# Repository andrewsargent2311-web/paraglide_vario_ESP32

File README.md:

# Paraglide Vario / Flight Computer (ESP32-S3)

A DIY flight computer for paragliding and paramotoring that costs about **$60 USD** in parts. It has a sunlight-readable screen, a climb/sink beeper (vario), GPS, a barometer, airspace warnings, live ADS-B traffic with spoken voice alerts, weather stations, FANET radio and IGC flight logging. Note the RLCD screen does not work well with polarized glasses (found that out on my first paragliding flight, use ski goggles on the paramotor).

**You do not need any electronics or programming experience.** This guide walks through every step. If you can follow a recipe and are willing to learn to solder a few small parts (or find a friend who can), you can build this.

> ⚠️ **Safety:** This is a hobby project, not a certified flight instrument. Never rely on it as your only source of airspace, altitude or traffic information. Test everything on the ground before you fly with it.

---

## Contents

1. [What it does](#1-what-it-does)
2. [What you need to buy](#2-what-you-need-to-buy)
3. [Tools you need](#3-tools-you-need)
4. [Step 1: Order the circuit board](#step-1-order-the-circuit-board)
5. [Step 2: 3D print the case](#step-2-3d-print-the-case)
6. [Step 3: Solder the circuit board](#step-3-solder-the-circuit-board)
7. [Step 4: Install VS Code and PlatformIO](#step-4-install-vs-code-and-platformio)
8. [Step 5: Add your WiFi details](#step-5-add-your-wifi-details)
9. [Step 6: Build and upload the code](#step-6-build-and-upload-the-code)
10. [Step 7: Prepare the SD card](#step-7-prepare-the-sd-card)
11. [Step 8: Assemble everything](#step-8-assemble-everything)
12. [Step 9: First power-on check](#step-9-first-power-on-check)
13. [How to use it](#how-to-use-it)
14. [Voice traffic alerts](#voice-traffic-alerts)
15. [Cloud base estimate](#cloud-base-estimate)
16. [Optional extras](#optional-extras)
17. [Troubleshooting](#troubleshooting)
18. [Using it outside New Zealand](#using-it-outside-new-zealand)
19. [Code layout](#code-layout)
20. [Credits](#credits)

---

## 1. What it does

- **Vario:** beeps faster and higher as you climb, lower tones when you sink
- **Main flight screen:** altitude, height above ground (AGL), ground speed, heading, QNH, battery
- **Airspace:** warns you about nearby controlled airspace from an OpenAIP file
- **Cloud base estimate:** a rough guess of how high the cloud base is, worked out from the temperature, humidity and pressure sensors (see [Cloud base estimate](#cloud-base-estimate))
- **ADS-B page:** shows nearby aircraft on a radar-style display, with an icon for each aircraft type, smooth movement between updates and automatic zoom (see [The traffic page](#the-traffic-page))
- **Voice traffic alerts:** when an aircraft comes close, the speaker tells you where it is, e.g. *"Aircraft on your two o'clock, flying north west, at two thousand four hundred feet, one thousand two hundred feet above you, and is eight hundred meters away."* You can switch this to a siren, or turn it off (see [Voice traffic alerts](#voice-traffic-alerts))
- **Weather page:** wind from nearby weather stations (Zephyr) or from FANET
- **FANET:** sends and receives FANET radio messages, with preset messages you can broadcast
- **IGC flight logging** to the SD card, downloadable over WiFi
- **Optional:** connects by Bluetooth to a separate engine meter (RPM, cylinder temperature) for paramotor use

**One button** controls everything (see [How to use it](#how-to-use-it)).

## 2. What you need to buy

| Part | Approx. cost | Notes |
|---|---|---|
| [Waveshare ESP32-S3-RLCD-4.2](https://www.waveshare.com/esp32-s3-rlcd-4.2.htm) | $35 USD (includes shipping, buy on Aliexpress) | The "brain", screen, speaker driver, SD slot and battery holder all in one |
| [Adafruit BMP580](https://www.adafruit.com/product/6411) | $10 USD | Barometer, measures altitude change for the vario |
| [Waveshare LC76G GNSS module](https://www.waveshare.com/lc76g-gnss-module.htm) | $15 | GPS |
| Custom circuit board (PCB) from PCBWay | $10 | See [Step 1](#step-1-order-the-circuit-board) |
| 3D printer filament (PLA) | $5 | Orange in the photos, any colour works |
| microSD card, 8–16 GB | a few $ | Doesn't need to be bigger |
| **HT-RA62 LoRa radio module** | $7 USD (includes shipping) | [HT-RA62] (https://heltec.org/project/ht-ra62/) Soldered directly onto the PCB, used for FANET. *Not included in the original $60 estimate.* |
| **18650 lithium battery** | comes with waveshare board for extra $3| Fits in the holder on the Waveshare board. Use a good-quality protected cell. |
| **USB-C data cable** | | Must carry data, not just charge |

**Small parts for the PCB** (all size 0805 surface-mount):

| Qty | Part |
|---|---|
| 2 | 100 nF capacitor |
| 2 | 10 µF capacitor |
| 1 | 10 kΩ resistor |

You will also need some pin headers and/or sockets to connect the Waveshare board, BMP580 and GPS module to the PCB. The exact layout is shown in the [KiCad project](PCB%20files/ESP32%20vario_PCB_layout/).

**Total: roughly $80 USD**

> **Tip:** Buy everything from the same order window if you can. PCBs from PCBWay usually arrive in a couple of weeks, so order that first.

## 3. Tools you need

- **Soldering iron** with a fine tip, solder and flux (for the tiny 0805 parts and the LoRa module). A hot-air station makes this easier but is not required.
- **Tweezers** (for the small parts)
- **A 3D printer**, or use a print service / friend with one
- **A computer** (Windows, Mac or Linux) with a USB port and an internet connection (the first build downloads a few hundred MB of tools)
- **A microSD card reader**
- Small screwdrivers, and wire cutters

**Never soldered before?** The only genuinely fiddly parts are the 0805 capacitors/resistor and the HT-RA62 module. Watch a couple of "how to solder SMD 0805" videos and practise on a spare board first, or ask a local maker space or electronics-savvy friend to do just those parts.

**Time:** allow a weekend. The 3D printing (about 9.5 hours total) runs by itself.

---

## Step 1: Order the circuit board

The circuit board (PCB) connects all the modules together so you don't have to wire anything by hand.

1. Go to [pcbway.com](https://www.pcbway.com) and choose **Instant Quote**.
2. Upload the file [`PCB files/Gerber Files V2/ESP32 vario-B_PCB_.zip`](PCB%20files/Gerber%20Files%20V2/). It contains all the Gerber and drill files in one zip.
3. Leave the options at their defaults unless you have a preference (it is a simple two-layer board), and place the order.

The original design files (KiCad) are in [`PCB files/ESP32 vario_PCB_layout/`](PCB%20files/ESP32%20vario_PCB_layout/) if you want to modify the board.

## Step 2: 3D print the case

All files are in [`3D print Files/`](3D%20print%20Files/).

| Part | STL file | Print time (0.15 mm PLA, Prusa MK3S) |
|---|---|---|
| Main case | `Flight computer main case.stl` | 5 h 49 m |
| Back plate | `Flight computer back plate.stl` | 2 h 11 m |
| Base plate | `Flight computer base plate.stl` | 1 h 14 m |
| Button | `button.stl` | 8 m |
| Button (short) | `button_Short.stl` | 6 m |
| Button (long) | `button_Long.stl` | 9 m |

- If you have a **Prusa MK3S**, you can print the ready-made G-code in the `Prusa slicer G code` folder.
- For **any other printer**, open the `.stl` files in your printer's slicing software (Cura, PrusaSlicer, Bambu Studio, etc.) and use normal PLA settings at 0.15 mm layer height.
- Print all three buttons; you'll pick whichever length feels best when you assemble it.

## Step 3: Solder the circuit board

Work from the smallest parts to the biggest, and take your time. Solder joints should be shiny and cone-shaped, not blobs.

1. **Small surface-mount parts first:** the two 100 nF capacitors, two 10 µF capacitors and the 10 kΩ resistor. The reference labels (C1, C2, C3, C-GPS1, R1) are printed on the board. Use the [parts list](PCB%20files/ESP32%20vario_PCB_layout/ESP32%20vario.csv) to match them.
2. **HT-RA62 LoRa module (U1):** solder this onto its pads on the board. Check the orientation using the silkscreen and the photo above. Double-check no pins are bridged with solder.
3. **Headers:** solder the pin headers/sockets for the Waveshare board (U2), BMP580 (U3) and GPS (U4).
4. **Plug in the modules.** Make sure each one goes the right way round. Use the photos in [`Photos/`](Photos/) as a reference.

**Before going on, check:** with a magnifier, look at every solder joint for bridges (solder connecting two neighbouring pins) and for pins that missed the solder.

## Step 4: Install VS Code and PlatformIO

This project is built with **[PlatformIO](https://platformio.org/)** inside **Visual Studio Code** (VS Code). PlatformIO downloads the ESP32 tools and every library the project needs automatically, so there is nothing to install by hand except VS Code and one extension. All of the board settings (PSRAM, USB serial, etc.) are already saved in the project's `platformio.ini` file, so you don't need to set anything.

### 4.1 Install VS Code
Download **Visual Studio Code** from [code.visualstudio.com](https://code.visualstudio.com/) and install it.

### 4.2 Install the PlatformIO extension
1. Open VS Code and click the **Extensions** icon in the left sidebar (it looks like four squares), or press `Ctrl+Shift+X` (`Cmd+Shift+X` on Mac).
2. Search for **PlatformIO IDE** and click **Install**.
3. Wait for it to finish (it can take a few minutes the first time, and a progress message appears at the bottom right), then **restart VS Code** when it asks.
4. After the restart you should see a new **alien-head PlatformIO icon** in the left sidebar and a blue bar of icons along the bottom of the window.

### 4.3 Download this project
Either:

- On this GitHub page, click the green **Code** button → **Download ZIP**, then unzip it somewhere you can find it (for example your Documents folder), **or**
- If you use Git: `git clone` this repository.

### 4.4 Open the project
1. In VS Code choose **File → Open Folder…**
2. Select the **top-level project folder**, the one that contains `platformio.ini` (not the `paraglide_vario_ESP32` folder inside it).
3. If VS Code asks *"Do you trust the authors of the files in this folder?"*, click **Yes, I trust the authors**.
4. PlatformIO now sets itself up. In the bottom-right you'll see messages such as *"Configuring project"* and *"Installing platform / libraries"*. **Wait until they finish.** The first time this downloads the ESP32 platform and all the libraries listed below, so it can take 5–15 minutes depending on your internet.

**Libraries installed for you automatically** (listed in `platformio.ini`; you never have to do this yourself):

| Library | Author |
|---|---|
| Adafruit BMP5xx | Adafruit |
| Adafruit SHTC3 | Adafruit |
| Adafruit Unified Sensor | Adafruit |
| ArduinoJson | Benoit Blanchon |
| NimBLE-Arduino | h2zero |
| RadioLib | Jan Gromeš |
| TinyGPSPlus | Mikal Hart |
| U8g2 (screen) | olikraus |
| Soldered PCF85063A RTC Library (clock) | Soldered |

> **Linux users:** to upload you need permission to use the USB serial port. Add yourself to the `dialout` group (`sudo usermod -aG dialout $USER`), then log out and back in. If it still can't see the board, install the PlatformIO udev rules (see the [PlatformIO docs](https://docs.platformio.org/en/latest/core/installation/udev-rules.html)).

## Step 5: Add your WiFi details

The code expects a file called `secrets.h` containing your WiFi network names and passwords. It is deliberately not uploaded to GitHub (so passwords don't leak), so you have to create it.

1. In VS Code's **Explorer** (the file list on the left, top icon in the sidebar), open the **`paraglide_vario_ESP32`** folder.
2. Right-click **`secrets.example.h`** → **Copy**, then right-click in an empty part of the same folder → **Paste**.
3. Right-click the copy (it will be named something like `secrets.example copy.h`) → **Rename**, and call it exactly **`secrets.h`**.
4. Open `secrets.h` and put in your details, for example:

```cpp
static const WifiNetwork WIFI_NETWORKS[WIFI_NETWORK_COUNT] = {
  { "MyHomeWiFi",     "my-home-password" },
  { "MyPhoneHotspot", "hotspot-password" },
  { "",               "" },
};
```

5. Save the file (`Ctrl+S`).

- Use a **2.4 GHz** network. The ESP32 can't connect to 5 GHz WiFi.
- Leave unused slots as empty quotes `""`.
- A **phone hotspot** is handy at the launch site, since that's how the ADS-B traffic and weather pages get their data in the field.
- You can also add networks later **from your phone, without reflashing**. See [Adding a WiFi network from your phone](#adding-a-wifi-network-from-your-phone).

## Step 6: Build and upload the code

1. Plug the Waveshare board into your computer with the USB-C data cable.
2. Look at the blue bar along the bottom of VS Code. The important icons are:

| Icon (hover to see its name) | What it does |
|---|---|
| ✓ **PlatformIO: Build** | Compiles the code without uploading it |
| → **PlatformIO: Upload** | Compiles and uploads to the board |
| 🔌 **PlatformIO: Serial Monitor** | Shows the messages the board prints (see Step 9) |

   You can also click the **PlatformIO (alien head) icon** in the left sidebar → **Project Tasks → esp32-s3 → General → Upload**.

3. Click **Upload** (the right-pointing arrow). The first build takes several minutes because it compiles every library.
4. When the terminal at the bottom says **`[SUCCESS]`**, the code is on your device. The board restarts by itself.

**What's already configured for you in `platformio.ini`** (you don't need to change any of this, but it's here in case you wonder):

| Setting | Value | Why |
|---|---|---|
| Board | `esp32-s3-devkitc-1` (ESP32-S3) | Matches the Waveshare board's chip |
| Platform | pioarduino (Arduino core 3.x for ESP32) | Required by the project's libraries |
| PSRAM | OPI PSRAM (`qio_opi` + `BOARD_HAS_PSRAM`) | The voice-alert clips are loaded into PSRAM |
| USB serial | `ARDUINO_USB_CDC_ON_BOOT=1` | Lets the Serial Monitor work over the USB-C port |
| Monitor speed | 115200 | Matches the code |

**If the upload doesn't start:** hold the **BOOT** button on the board, tap **RESET**, then release BOOT, and click Upload again. PlatformIO finds the port automatically. If you have several USB serial devices plugged in and it picks the wrong one, you can add a line such as `upload_port = COM5` (Windows) or `upload_port = /dev/ttyACM0` (Linux/Mac) under `[env:esp32-s3]` in `platformio.ini`.

> **Ignore the `native` environment.** `platformio.ini` also contains an `[env:native]` section. That is only for running the code's unit tests on a PC (`pio test -e native`) and isn't used when building for the device. If PlatformIO asks which environment to use, choose **esp32-s3**.

## Step 7: Prepare the SD card

1. **Format** the microSD card as **FAT32**.
2. Copy the files you want from [`paraglide_vario_ESP32/Goes into SD card/`](paraglide_vario_ESP32/Goes%20into%20SD%20card/) onto the **root** of the card. The two files go straight onto the card, but the **`VOICE` folder must be copied as a folder**, with the clips inside it:

| File / folder | What it's for |
|---|---|
| `AIRSPACE.txt` | Airspace data, used for warnings |
| `Lower_North_Island.ADEM` | Terrain height map, used to work out your height above ground (AGL). It's about 99 MB. |
| `VOICE/` (folder) | The 60 short speech clips (`V000.PCM` to `V059.PCM`) used for [voice traffic alerts](#voice-traffic-alerts). Flat `/VOICE/V###.PCM` files are the **Default** voice; optional profiles go in subfolders such as `/VOICE/US_RYAN/V000.PCM`. |

3. Eject the card safely and put it into the microSD slot on the Waveshare board.

**Notes:**
- The vario still works without the SD card, but you won't get flight logs, maps, airspace or voice alerts.
- All 60 clips must be present in a profile folder or that profile is skipped. The existing flat `/VOICE/V###.PCM` layout is still supported as **Default**. Put additional voices in `/VOICE/<NAME>/` folders; profile names may use letters, numbers, `_` and `-`, up to 12 characters. The device can list up to 8 profiles. `manifest.txt` is just a list of what each clip says and is ignored by the device.
- Generate additional profiles with the [`voicebuild` tool](voicebuild/README.md). Copy each generated profile folder into `VOICE/` on the card.
- You can keep several `.ADEM` maps on the card and choose between them from the menu (**Map**).
- The included airspace and terrain files cover the lower North Island of New Zealand. See [Optional extras](#optional-extras) for other areas.
- An optional splash image can be shown at startup: a file called `ROY.BIN` in the card root, a full-screen 300 × 400 black-and-white image of exactly 15,200 bytes. If it's missing or a different size, a plain text splash screen is shown instead, so you can skip this.

## Step 8: Assemble everything

1. Fit the **18650 battery** into the holder on the Waveshare board (check the +/− direction printed on the holder).
2. Plug the **speaker** into its 2-pin socket.
3. Push the Waveshare board onto the PCB, making sure the pins are lined up.
4. Connect the GPS and BMP580 modules to the PCB, and attach the antenna to the LoRa module.
5. Fit the board sandwich into the 3D-printed **main case**, then close it with the **back plate** and **base plate**.
6. Push the printed **button** into place over the button on the board. Try the three button lengths and use whichever feels best.

The GPS "bump" on the case (marked "GPS") should face the sky when you hold the unit flat, so the GPS gets a clear view.

Look at the photos in the [`Photos/`](Photos/) folder if you're unsure how something fits.

## Step 9: First power-on check

Do this indoors first, then repeat outside.

1. Switch on / plug in the unit. The **splash screen** appears for about 3 seconds, then the main screen.
2. Move the unit up and down by about a metre. You should hear the **vario beep** and see the altitude change.
3. Take it **outside with a clear view of the sky**. The first GPS lock can take a few minutes. Once it locks, speed, heading and time appear.
4. Look at the **AIR SPACE** box on the main screen. After the first temperature/humidity reading (about 10 seconds) and once the GPS has calibrated the altitude, the **CLD BASE** line shows a number. Until then it shows `--`. See [Cloud base estimate](#cloud-base-estimate) to calibrate it.
5. To see what the device is doing while it boots, click the **Serial Monitor** (🔌 plug icon) in the blue bar at the bottom of VS Code while the unit is plugged into your computer. It runs at **115200** baud automatically. It prints messages showing whether the SD card, barometer, GPS and radio all started correctly. If voice clips loaded you will see `[Voice] Loaded 60 voice clips into PSRAM (profile: Default)` or the name of the selected profile. Click the bin/trash or press `Ctrl+C` in the terminal to close the monitor, and **close it before you upload again** (the upload can't use the port while the monitor has it open).

---

## How to use it

The unit has **one button**:

| Menu | Press | What happens |
|---|---|---|
| Closed | **Short press** | Switch to the next page (Glider → Wind → ADS-B) |
| Closed | **Double press** | Open the menu |
| Closed | **Hold ~4 seconds** | Mute / unmute the vario |
| Open | **Short press** | Move down to the next menu item |
| Open | **Hold ~2 seconds** | Select the highlighted item |
| Open | **Double press** | Go back one level (or close the menu from the top level) |

**Menu contents**

- **Main Page:** choose Paraglider or Paramotor as the first page
- **Config:** time zone, units (altitude / speed), main volume, vario beep (climb and sink volume), lift threshold (climb beeps start above this: 0.0–1.0 m/s in 0.1 steps, default 0.1), screen orientation
- **Connections:** WiFi on/off, network choice, **Add Network** and **Forget Network** (see below), Bluetooth (engine meter), FANET on/off
- **FANET Messaging:** messaging on/off, and the preset messages you can broadcast
- **Map:** choose which terrain map to use
- **ADS-B settings:** alert radius and vertical threshold, auto-jump to the ADS-B page, **Alarm Sound** (Off / Alarm / Voice), **Alert Volume**, range rings, airspace bars, **Voice** profile, **Ground Traffic** and **Labels** (see [The traffic page](#the-traffic-page))
- **Weather settings:** update interval, number of stations, data source
- **Flight recordings:** recording on/off, **Export files** (see below), auto-stop, **Flights** (see below)

**Flight logs:** the unit automatically starts recording an `.IGC` file when you start moving (above about 10 km/h for 10 seconds). To download logs, open **Flight recordings → Export files**. Once the unit is connected to WiFi it shows a web address (something like `http://192.168.x.x/`). Open that in a browser on a phone or computer on the same network and click the file to download. If the server can't start, the screen tells you why: **WiFi not connected**, or **No SD card** (insert one and restart the unit, as it only checks for a card when it starts up).

The same page also lets you:
- **Delete** old flight recordings (asks to confirm first).
- **Upload** a new `.ADEM` terrain map or a replacement `AIRSPACE.txt` straight to the SD card, so you don't need to take the card out. Large maps take several minutes over WiFi, so do it on the ground. Then pick the new map from **Menu → Map**. After replacing `AIRSPACE.txt`, restart the unit, as airspace only loads at start-up.
- **Delete** maps you no longer need (the map currently in use can't be deleted or replaced; choose a different one in the Map menu first).

A script can load the rest of a card over the same connection. `POST /upload?path=ROY.BIN` or `POST /upload?path=VOICE/US_LESSAC/V000.PCM` (a multipart form with a `file` field) adds the splash image and voice files, creating the voice folders if needed. `GET /list` returns every file's path and size for checking. Restart the unit afterwards so it loads them.

Deleting and uploading are switched off while a flight is being recorded. Tracks are recorded at **one point per second**.

**Flights:** **Flight recordings → Flights** lists your 12 most recent flights, newest first, with the date, take-off time, duration, maximum altitude and best climb. Take-off time is when recording started, so it may be earlier than your actual take-off if the unit was already moving, for example in a car on the way to launch. Summaries are saved to `FLIGHTS.CSV` on the SD card about once a minute during a flight, so turning the unit off loses at most the last minute of the summary, and the IGC file itself isn't affected. Flights recorded before this feature show only the date, time and duration.

---

## Adding a WiFi network from your phone

You can add a network (for example a friend's hotspot, or the WiFi at a new launch site) straight from the unit, with no computer needed.

1. Open **Menu → Connections → WiFi → + Add Network**. The unit scans for nearby networks, then starts its own temporary WiFi hotspot called **`Vario-Setup`**. The screen shows two steps side by side, each with a QR code, and a status line underneath that tells you which step to do next.
2. **Step 1 (left):** on your phone, scan the left QR code to join the hotspot, or join the **`Vario-Setup`** WiFi network by hand using the password **`GetHigh!`**.
3. **Step 2 (right):** scan the right QR code, or open a browser and go to **`192.168.4.1`**. Some phones open the setup page by themselves after step 1, in which case you can skip this.
4. Tap your network in the list (or choose **Other / hidden network** and type its name), enter the password and tap **Save & connect**.
5. The hotspot closes and the unit connects to the new network. The menu shows **Saved: *network name***. Your phone goes back to its normal WiFi.

Notes:
- The unit remembers up to **5** networks added this way, on top of the ones in `secrets.h`. They are kept through reboots **and** firmware updates. When all 5 are used, the oldest is replaced.
- Saving a network that is already stored updates its password, so this is also how you fix a wrong password.
- **Connections → WiFi → − Forget Network** removes a network added this way. Networks in `secrets.h` can only be changed by editing that file and uploading again.
- The `Vario-Setup` hotspot uses WPA2 with the password `GetHigh!`, and only runs while the Add Network screen is in use. It closes on **Cancel**, after a network is saved, or after 10 minutes of inactivity.
- If the setup page closes on your phone, open **`192.168.4.1`** in your browser again.
- If the setup page won't open, or your phone keeps dropping the `Vario-Setup` WiFi, turn mobile data off until you've finished. The hotspot has no internet, so some phones leave it or try to use mobile data instead. The unit's screen shows this reminder too.
- Normal WiFi (ADS-B, weather, Export Files) pauses while the hotspot is up.
- The unit can only use **2.4 GHz** networks. Set phone hotspots to 2.4 GHz.

## The traffic page

The ADS-B page shows aircraft around you, from adsb.fi over WiFi and from FANET radio.

- **Icons:** light aircraft, jet/airliner, helicopter, glider, paraglider and hang glider, each turned to show which way it's heading. If the type isn't known, it shows as a light aircraft. ADS-B can't tell a paraglider from a hang glider or ultralight, so those all show as a paraglider. FANET reports the exact type.
- **Movement:** between updates, each aircraft moves forward using its last speed and track. After 30 seconds with no update it changes to an **outline**, meaning its position is only an estimate. After 60 seconds it's removed.
- **Close traffic:** an airborne ADS-B aircraft within 5 km and 4,000 ft gets a flashing double ring and a black label with white text. Aircraft on the ground never flash. FANET traffic doesn't flash either, because pilots flying together are often this close. Voice and siren alerts have their own distances, in **ADSB Settings**.
- **Range and zoom:** the widest view is your **Range Rings** setting. The page zooms in to 30, 10 or 5 km to fit the nearest aircraft within 3,000 ft of your altitude. It zooms in straight away, and waits 10 seconds before zooming back out. Other aircraft are still drawn if they're in view, but don't affect the zoom. The ring labels always show the current range.
- **Ground traffic:** **ADSB Settings → Ground Traffic: Hide/Show** (default Hide). Hide removes ADS-B aircraft reported as on the ground, or below 200 ft and slower than 40 kt. Helicopters and FANET traffic are never hidden, and airborne traffic shows at any altitude. This doesn't change voice or siren alerts.
- **Labels:** **ADSB Settings → Labels: Relevant/All/Off** (default Relevant). Relevant labels aircraft within 7,000 ft of your altitude, All labels every aircraft, and Off shows icons only. Relevant and All both stop at **8 labels**: close traffic first, then the nearest, and the rest show as icons. Each label goes on whichever side of its icon is clear. In a tight group it may sit further out, with a thin line back to its aircraft.
- **Whole-screen view:** aircraft and airspace lines fill the area below the top bar, past the outer range ring and into the corners. The altitude, speed and climb boxes move clear of the banners.
- **Airspace lines:** **ADSB Settings → Airspace Lines** opens separate **Controlled**, **CFZ** and **MBZ** toggles (all On by default). Turning a group off hides only its dashed lines; the Airspace Info bar continues to list and cycle nearby airspaces regardless of toggles, and draws the one it describes solid and thick. All three groups off means no dashed lines. Lines need a GPS fix. With **Airspace Info** on, the bottom bar steps through up to 8 nearby airspaces, 8 seconds each. It shows the name, class, limits and either its distance and direction or where you are relative to it (**IN IT**, **BELOW IT**, **ABOVE IT**), with its place in the list at the right. Airspace you're in comes first. Airspace warnings are unchanged.
- **Compass and range:** the N, E, S and W letters and the ring distances are drawn on top of everything, so aircraft and labels can't cover them.

When there's nothing to plot, the page says why:

| Message | Meaning |
|---|---|
| **Waiting for GPS fix** | The unit hasn't had a GPS position yet |
| **Reconnecting to WiFi / No traffic data** | The unit isn't connected to WiFi, so it can't get ADS-B traffic |
| **No internet / No traffic data** | WiFi is connected, but the last download failed |
| **Reconnecting / No traffic data** | WiFi is connected, but there's been no good download for over 35 seconds |
| **WiFi off / No traffic data** | WiFi is turned off in the menu |
| **Checking for traffic** | Waiting for the first download to finish |
| **No traffic within N km** | A recent download worked and nothing is in range. N is your Range Rings setting |

"No traffic data" means the unit can't tell, so aircraft may still be there. The Weather page has its own GPS, WiFi and internet messages.

**If the connection drops:** ADS-B aircraft stay on the page for up to 2 minutes, as outlines still moving along their last track, and a message at the bottom right says **Reconnecting...**. Treat these positions as rough estimates: an aircraft may have turned. The unit keeps trying to reconnect by itself, every 20 seconds at first and then every minute. If it's still joined to the network but three traffic downloads in a row fail (about 45 seconds), it restarts the connection, and **Connections → WiFi** shows **no internet** rather than **connected**.

## Voice traffic alerts

When ADS-B shows an aircraft close to you, the unit can **speak** the warning (or sound a siren) as well as showing it on screen. For example:

> *"Aircraft on your two o'clock, flying north west, at two thousand four hundred feet, one thousand two hundred feet above you, and is eight hundred meters away."*

**Turning it on and setting it up** (all under **ADSB Settings** in the menu):

| Item | What it does |
|---|---|
| **Alarm Sound** | Select it (hold the button ~2 seconds) to cycle **Off → Alarm → Voice**; each select moves it to the next mode. *Alarm* is the two-tone siren (5 seconds). *Voice* speaks the sentence above. *Off* mutes both. |
| **Alert Volume** | How loud the alert is, 0–100% in 10% steps. It applies to whichever of Alarm or Voice is selected. Select **Test** at the bottom of the list to hear it (it plays the example sentence above). It deliberately does not play a preview each time you scroll, because the full sentence takes about 5 seconds. |
| **Voice** | Select to cycle through the available profiles, including **Default** for the original flat `/VOICE/V###.PCM` clips. Switching takes a couple of seconds; the menu shows **Loading...** while it changes. The successful choice is remembered across reboots. |
| **Alert Radius** | How close, sideways, an aircraft must be to trigger an alert: 3, 5, 8 or 10 km (default 5). |
| **Vertical Threshold** | How close, up or down, it must be: 1000, 1500, 2000 or 3000 ft (default 2000). |
| **Auto-Jump** | Whether a new aircraft also switches the screen to the ADS-B page. This only changes the screen. The audio alert happens either way. |

**What it tells you, in order:**

1. **Where it is** as a clock position relative to the direction you are travelling (12 o'clock is straight ahead, 3 is to your right, 9 to your left).
2. **Which way it is flying** as a compass direction (north, north east, and so on). If the aircraft isn't broadcasting a heading it says *"heading unknown"*.
3. **Its altitude**, rounded to the nearest 100 ft.
4. **How far above or below you** it is, rounded to the nearest 100 ft.
5. **How far away** it is: in metres (nearest 100) when it is under 2 km, or in whole kilometres from 2 km up.

**When it speaks:**
- **Straight away** when a new aircraft enters your alert radius and vertical band.
- **Again every 60 seconds** for as long as an aircraft is still inside that zone. Each alert restarts the 60-second wait.
- It always describes the **nearest** aircraft, which is not necessarily the one that triggered the alert.
- It plays over the vario tone while it is speaking, and the vario carries on afterwards.

**Good to know:**
- **It needs a GPS fix and for you to be moving.** The clock position is worked out from your direction of travel, so with no valid GPS course (for example standing still on the ground, or before the first fix) the voice alert stays silent rather than guess. The siren does not have this limit.
- **It needs the SD card with the `VOICE` folder** (see [Step 7](#step-7-prepare-the-sd-card)) and **PSRAM enabled**, which the project's `platformio.ini` already does for you (see [Step 6](#step-6-build-and-upload-the-code)). The selected profile is loaded into memory at start-up; nothing is read from the card while an alert is playing. Switching profiles reads the clips in the background and can take a couple of seconds.
- ADS-B data arrives over WiFi, so the alert only works when the unit is connected (for example to your phone hotspot). See the notes on ADS-B in [Step 5](#step-5-add-your-wifi-details).
- Like the rest of this project it is an aid, not a safety system. Keep looking around.

## Cloud base estimate

The **AIR SPACE** box on the Glider and Paramotor pages has a third line under the nearest-airspace distances:

```
VERT: 3200ft
HORI: 4.5km
BASE: 4200ft
```

**What it means:** a rough estimate of the height of the cloud base, shown as an altitude above sea level in your chosen units, so you can compare it directly with your altitude reading. It shows `--` until the altitude is calibrated, and `0` means you are at or inside cloud.

**How it works:** the temperature and humidity sensor on the Waveshare board gives the *dew point*. The gap between the air temperature and the dew point tells you how far the air has to rise before it cools enough to form cloud (roughly 125 m of height per 1°C of gap). The barometer's pressure reading is used to convert that into a height. It updates every 10 seconds and is smoothed so the number doesn't jump around.

**Good to know:**
- It is a **rough guide**, best for daytime cumulus-type conditions where the air is well mixed. It is not meaningful in stable or layered conditions, and it becomes less accurate the higher the base is.
- Don't rely on it as your only source of cloud information.
- The sensor is inside the case, so it lags behind the real air when conditions change quickly.

### Calibrate it (recommended)

The temperature sensor sits next to the processor and battery, so it reads **warmer than the outside air**. This makes the cloud base read **too high**, by about **125 m for every 1°C** of error. You can fix this with one number:

1. Switch the unit on and leave it for about **10 minutes** so it warms up to normal.
2. Compare the temperature on the unit with a trusted thermometer (or a nearby weather station) in the same conditions. Ideally do this outdoors, in the shade.
3. Work out the difference. For example, the unit says 24°C and the thermometer says 21°C, so the difference is **3.0**.
4. In VS Code, press `Ctrl+P` (`Cmd+P` on Mac), type **`AuxSensors.h`** and press Enter to open it. Then press `Ctrl+F` and search for `SHT_SELF_HEAT_OFFSET_C`.
5. Change the number after it (the default is `0.0f`), for example:

```cpp
#define SHT_SELF_HEAT_OFFSET_C 3.0f
```

6. Save the file (`Ctrl+S`) and click **Upload** again (see [Step 6](#step-6-build-and-upload-the-code)).

The dew point is not affected by the self-heating, so only this one number needs adjusting. If you can, compare the estimate against real cloud bases on a few flights and adjust the offset until it looks right.

The estimate needs no extra parts or libraries. It uses the sensors already on the board and is calculated in the `CloudBase.h` file in the code folder.

---

## Optional extras

### Get airspace for your own area
1. Go to [openaip.net](https://www.openaip.net/) and crop the airspace for your region.
2. Export it in **OpenAir `.txt`** format.
3. Rename it **`AIRSPACE.txt`** and put it in the root of the SD card, replacing the old one.
4. Very large files can cause problems. Crop to a sensible area around where you fly.

### Get more terrain maps
- Ready-made maps are in this shared folder: [Google Drive maps](https://drive.google.com/drive/folders/18hl1OCvvLns53WSxIf6_7ccbEHTFu314?usp=sharing). Download the `.ADEM` file you want and copy it to the SD card.
- To make your own from a New Zealand LINZ elevation download (GeoTIFF), use the Python script [`dem_to_agldem.py`](paraglide_vario_ESP32/dem_to_agldem.py). The script's comments explain how it works.

### Engine meter (paramotor)
The [`Engine_meter/`](Engine_meter/) folder contains a separate project (nRF52840-based) that measures RPM and cylinder head temperature and sends them to the flight computer over Bluetooth. It is not needed for paragliding.

---

## Troubleshooting

| Problem | Try this |
|---|---|
| **The PlatformIO icon / blue bar doesn't appear** | Make sure the **PlatformIO IDE** extension is installed, then restart VS Code. Also make sure you opened the **top-level folder** that contains `platformio.ini` (File → Open Folder). |
| **"Installing platform/libraries" fails or hangs** | You need a working internet connection, and GitHub must be reachable (the ESP32 platform is downloaded from there). Check your connection or VPN/firewall, then run **PlatformIO → Project Tasks → esp32-s3 → General → Clean** and build again. |
| **Can't find a COM port / upload won't start** | Use a USB cable that carries data (many are charge-only). Hold BOOT, tap RESET, release BOOT, then upload again. Close the Serial Monitor before uploading. On Linux, check the `dialout` group note in [Step 4](#step-4-install-vs-code-and-platformio). |
| **Error: `secrets.h: No such file or directory`** | You skipped [Step 5](#step-5-add-your-wifi-details). Copy `secrets.example.h` to `secrets.h` inside the `paraglide_vario_ESP32` folder. |
| **Error about `PCF85063A.h`, `U8g2` or another missing file** | A library didn't install properly. Run **PlatformIO → Project Tasks → esp32-s3 → General → Clean**, then **Build** again. If it still fails, delete the hidden `.pio` folder in the project and build again so every library is downloaded fresh. |
| **Error mentioning `U8G2_ST7305_300X400…`** | The screen library didn't download correctly or is an old version. Delete the `.pio` folder and build again (this forces a fresh download of the latest U8g2). |
| **Screen stays blank or code crashes on boot** | Check that `platformio.ini` still contains `board_build.arduino.memory_type = qio_opi` and `-DBOARD_HAS_PSRAM`. Open the Serial Monitor to see the error message. |
| **No sound** | Check the speaker is plugged in and the vario isn't muted (hold the button ~4 s). Check volume in **Config → Volume**. Traffic alerts have their own level in **ADSB Settings → Alert Volume**. |
| **No GPS fix** | Go outside with a clear view of the sky and wait a few minutes. Check the GPS module's soldering and that the case doesn't block it. |
| **No voice alert (siren works, or nothing plays)** | Check **ADSB Settings → Alarm Sound** is set to **Voice** (not Alarm or Off) and the Alert Volume isn't 0%. Then check the Serial Monitor at boot for `[Voice] Loaded 60 voice clips into PSRAM`. |
| **Serial Monitor says `[Voice] /VOICE folder not found` or a profile is incomplete** | The `VOICE` folder must sit in the root of the SD card. The flat Default clips go directly inside it; each named profile needs all 60 clips (`V000.PCM` to `V059.PCM`) in its own subfolder. Incomplete profiles are skipped. |
| **Serial Monitor says `[Voice] PSRAM allocation failed`** | PSRAM isn't enabled in the build. Check the PSRAM lines in `platformio.ini` (see [Step 6](#step-6-build-and-upload-the-code)) and upload again. |
| **Serial Monitor shows nothing** | Make sure the unit is plugged in with a data cable, that you've clicked the plug icon, and that `-DARDUINO_USB_CDC_ON_BOOT=1` is still in `platformio.ini`. Try unplugging and replugging the USB cable. |
| **Voice alert works in the menu Test but never speaks in flight** | It stays silent until the GPS has a valid course, so you need a fix and to be moving. It also needs WiFi for the ADS-B data, and the aircraft must be inside your Alert Radius and Vertical Threshold. |
| **Altitude doesn't change / vario silent** | The BMP580 isn't being detected. Check its soldering and orientation. The Serial Monitor will report this on boot. |
| **SD card not detected** | Make sure it's FAT32, and files are in the root, not inside a folder. Try a different (smaller) card. |
| **WiFi won't connect** | 2.4 GHz only. Check the name and password in `secrets.h` match exactly (they're case-sensitive), then re-upload. |
| **CLD BASE shows `--`** | It needs a calibrated altitude (wait for a GPS fix) and a working barometer and temperature/humidity sensor. Give it about 10–20 seconds after start-up. |
| **CLD BASE reads much too high** | The temperature sensor is reading warm from the board's heat. Set `SHT_SELF_HEAT_OFFSET_C`; see [Cloud base estimate](#cloud-base-estimate). |
| **Menu doesn't open with a double press** | Press twice more quickly, or adjust `MENU_DOUBLE_PRESS_MS` in `menu.h`. |
| **No FANET / radio not working** | Check the HT-RA62 soldering and antenna. |

Still stuck? Open an **Issue** on this GitHub page, include what you were doing, what you expected and what happened, and copy in the messages from the Serial Monitor.

---

## Using it outside New Zealand

The code is set up for New Zealand, so a few things need changing elsewhere:

- **FANET radio frequency** is set to 868.2 MHz (NZ). Other regions differ (for example Australia uses the 915–928 MHz band). It's set where `fanetRadio.begin(` is called, which appears in both `FlightComputer.cpp` and `FanetHandlers.cpp`, so change both. In VS Code, press `Ctrl+Shift+F` and search for `fanetRadio.begin(` to find them. **Check your local rules before changing it.**
- **Weather stations** come from Zephyr (`api.zephyrapp.nz`), which only covers NZ. FANET weather still works anywhere.
- **Terrain maps** are built from NZ LINZ data. The conversion script would need different source data elsewhere.
- **Time zone** defaults to NZ (with daylight saving); you can set a fixed offset in **Config → Time**.
- **ADS-B** uses the worldwide adsb.fi service and airspace uses OpenAIP, so those work anywhere.
- **Voice alerts** are in English, in feet and metres/kilometres, and work anywhere. To change the words you would need to regenerate the 60 clips and `VoiceClips.h` together so they stay in step.

---

## Code layout

The firmware lives in `paraglide_vario_ESP32/` and is split into one `.h`/`.cpp` pair per subsystem. `FlightComputer.cpp` holds only the includes, `setup()` and `loop()`. You don't need any of this to build the project, but it helps if you want to change something. In VS Code, `Ctrl+P` lets you jump to any file by name, and `Ctrl+Shift+F` searches across all files.

| File | What it does |
|---|---|
| `FlightComputer.cpp` | The start-up (`setup()`) and main loop (`loop()`) |
| `Buzzer` | Speaker and audio chip: vario beeps, sink tone, siren, mute jingle, and the voice alert trigger (`triggerAdsbAlert()`) |
| `VoiceAlert`, `VoiceClips.h` | Voice alerts: loads the 60 clips from the SD card into PSRAM at start-up, builds the spoken sentence and plays it |
| `AdsbClient` | Fetches and parses ADS-B traffic and works out which aircraft are threats |
| `Vario`, `WindEstimator` | Barometer, altitude and climb rate; wind estimate |
| `AuxSensors`, `CloudBase.h` | Battery, temperature/humidity sensor (cloud base estimate) and the clock |
| `FanetHandlers`, `Fanet`, `FanetMessaging`, `Sx126xLink` | FANET radio |
| `WeatherClient` | Weather station data |
| `Gps`, `SdCard`, `Display`, `IgcRecorder` | GPS object, SD card, screen, flight logging |
| `BackgroundTask` | The second processor core: WiFi, Bluetooth, web file server, ADS-B and weather polling, terrain and airspace lookups |
| `wifi_manager`, `WifiSetup` | WiFi connection and saved networks; the `Vario-Setup` phone portal for adding networks from the device |
| `PageButton`, `menu`, `settings`, `DrawPages` | The single button, the menus, saved settings and drawing the pages |

## Credits

Designed and built by Andrew Sargent, including the PCB and case design. The code was written with help from Claude, GPT-5, Gemini and Copilot, plus code from other projects on GitHub. The voice alert clips were generated offline with the [Piper](https://github.com/rhasspy/piper) neural text-to-speech engine. Thanks to everyone whose open-source work this builds on.

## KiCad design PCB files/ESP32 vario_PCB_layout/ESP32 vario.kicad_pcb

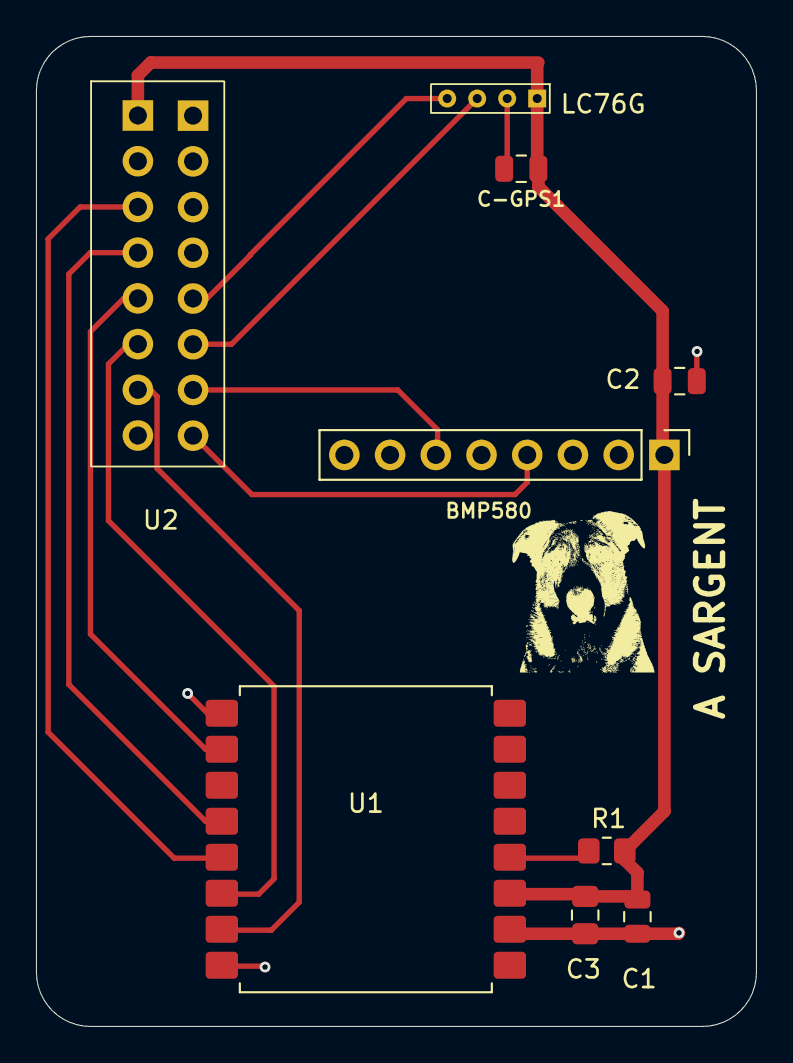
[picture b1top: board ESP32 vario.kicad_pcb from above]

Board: 2 copper layers, 40.0 x 55.0 mm, 9 parts (0 on the bottom side), 12 nets.

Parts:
BMP580: BMP580; PinHeader_1x08_P2.54mm_Vertical
C1, C2: 10u; C_0805_2012Metric
C3: 100n; C_0805_2012Metric_Pad1.18x1.45mm_HandSolder
C-GPS1: 100n; C_0805_2012Metric
LC76G: LC76G GPS; LC76G- 4 pin
R1: 10K; R_0805_2012Metric_Pad1.20x1.40mm_HandSolder
U1: HT-RA62
U2: ESP32-S3 Waveshare; ESP32-S3 Waveshare 16pin header

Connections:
+3V: BMP580.1 (Vin), C1.2, C2.1, C3.2, C-GPS1.1, LC76G.1 (Vcc), R1.1, U1.3 (3V3), U2.1 (3V)
BUSY: U1.10 (BUSY), U2.5 (GP2)
GND: BMP580.3 (GND), C1.1, C2.2, C3.1, C-GPS1.2, LC76G.2 (GND), U1.2 (GND), U1.9 (GND), U1.16 (GND), U2.2 (GND), U2.10 (GND)
MISO: U1.13 (MISO), U2.3 (GP0)
MOSI: U1.14 (MOSI), U2.6 (GP3)
NSS(CS): U1.15 (NSS), U2.7 (GP17)
RST: R1.2, U1.4 (RST)
Rx: LC76G.3 (tX), U2.14 (Rx44)
SCK: U1.12 (SCK), U2.4 (GP1)
SCL: BMP580.4 (SCL), U2.16 (SCL)
SDA: BMP580.6 (SDA), U2.15 (SDA)
Tx: LC76G.4 (Rx), U2.13 (Tx43)
